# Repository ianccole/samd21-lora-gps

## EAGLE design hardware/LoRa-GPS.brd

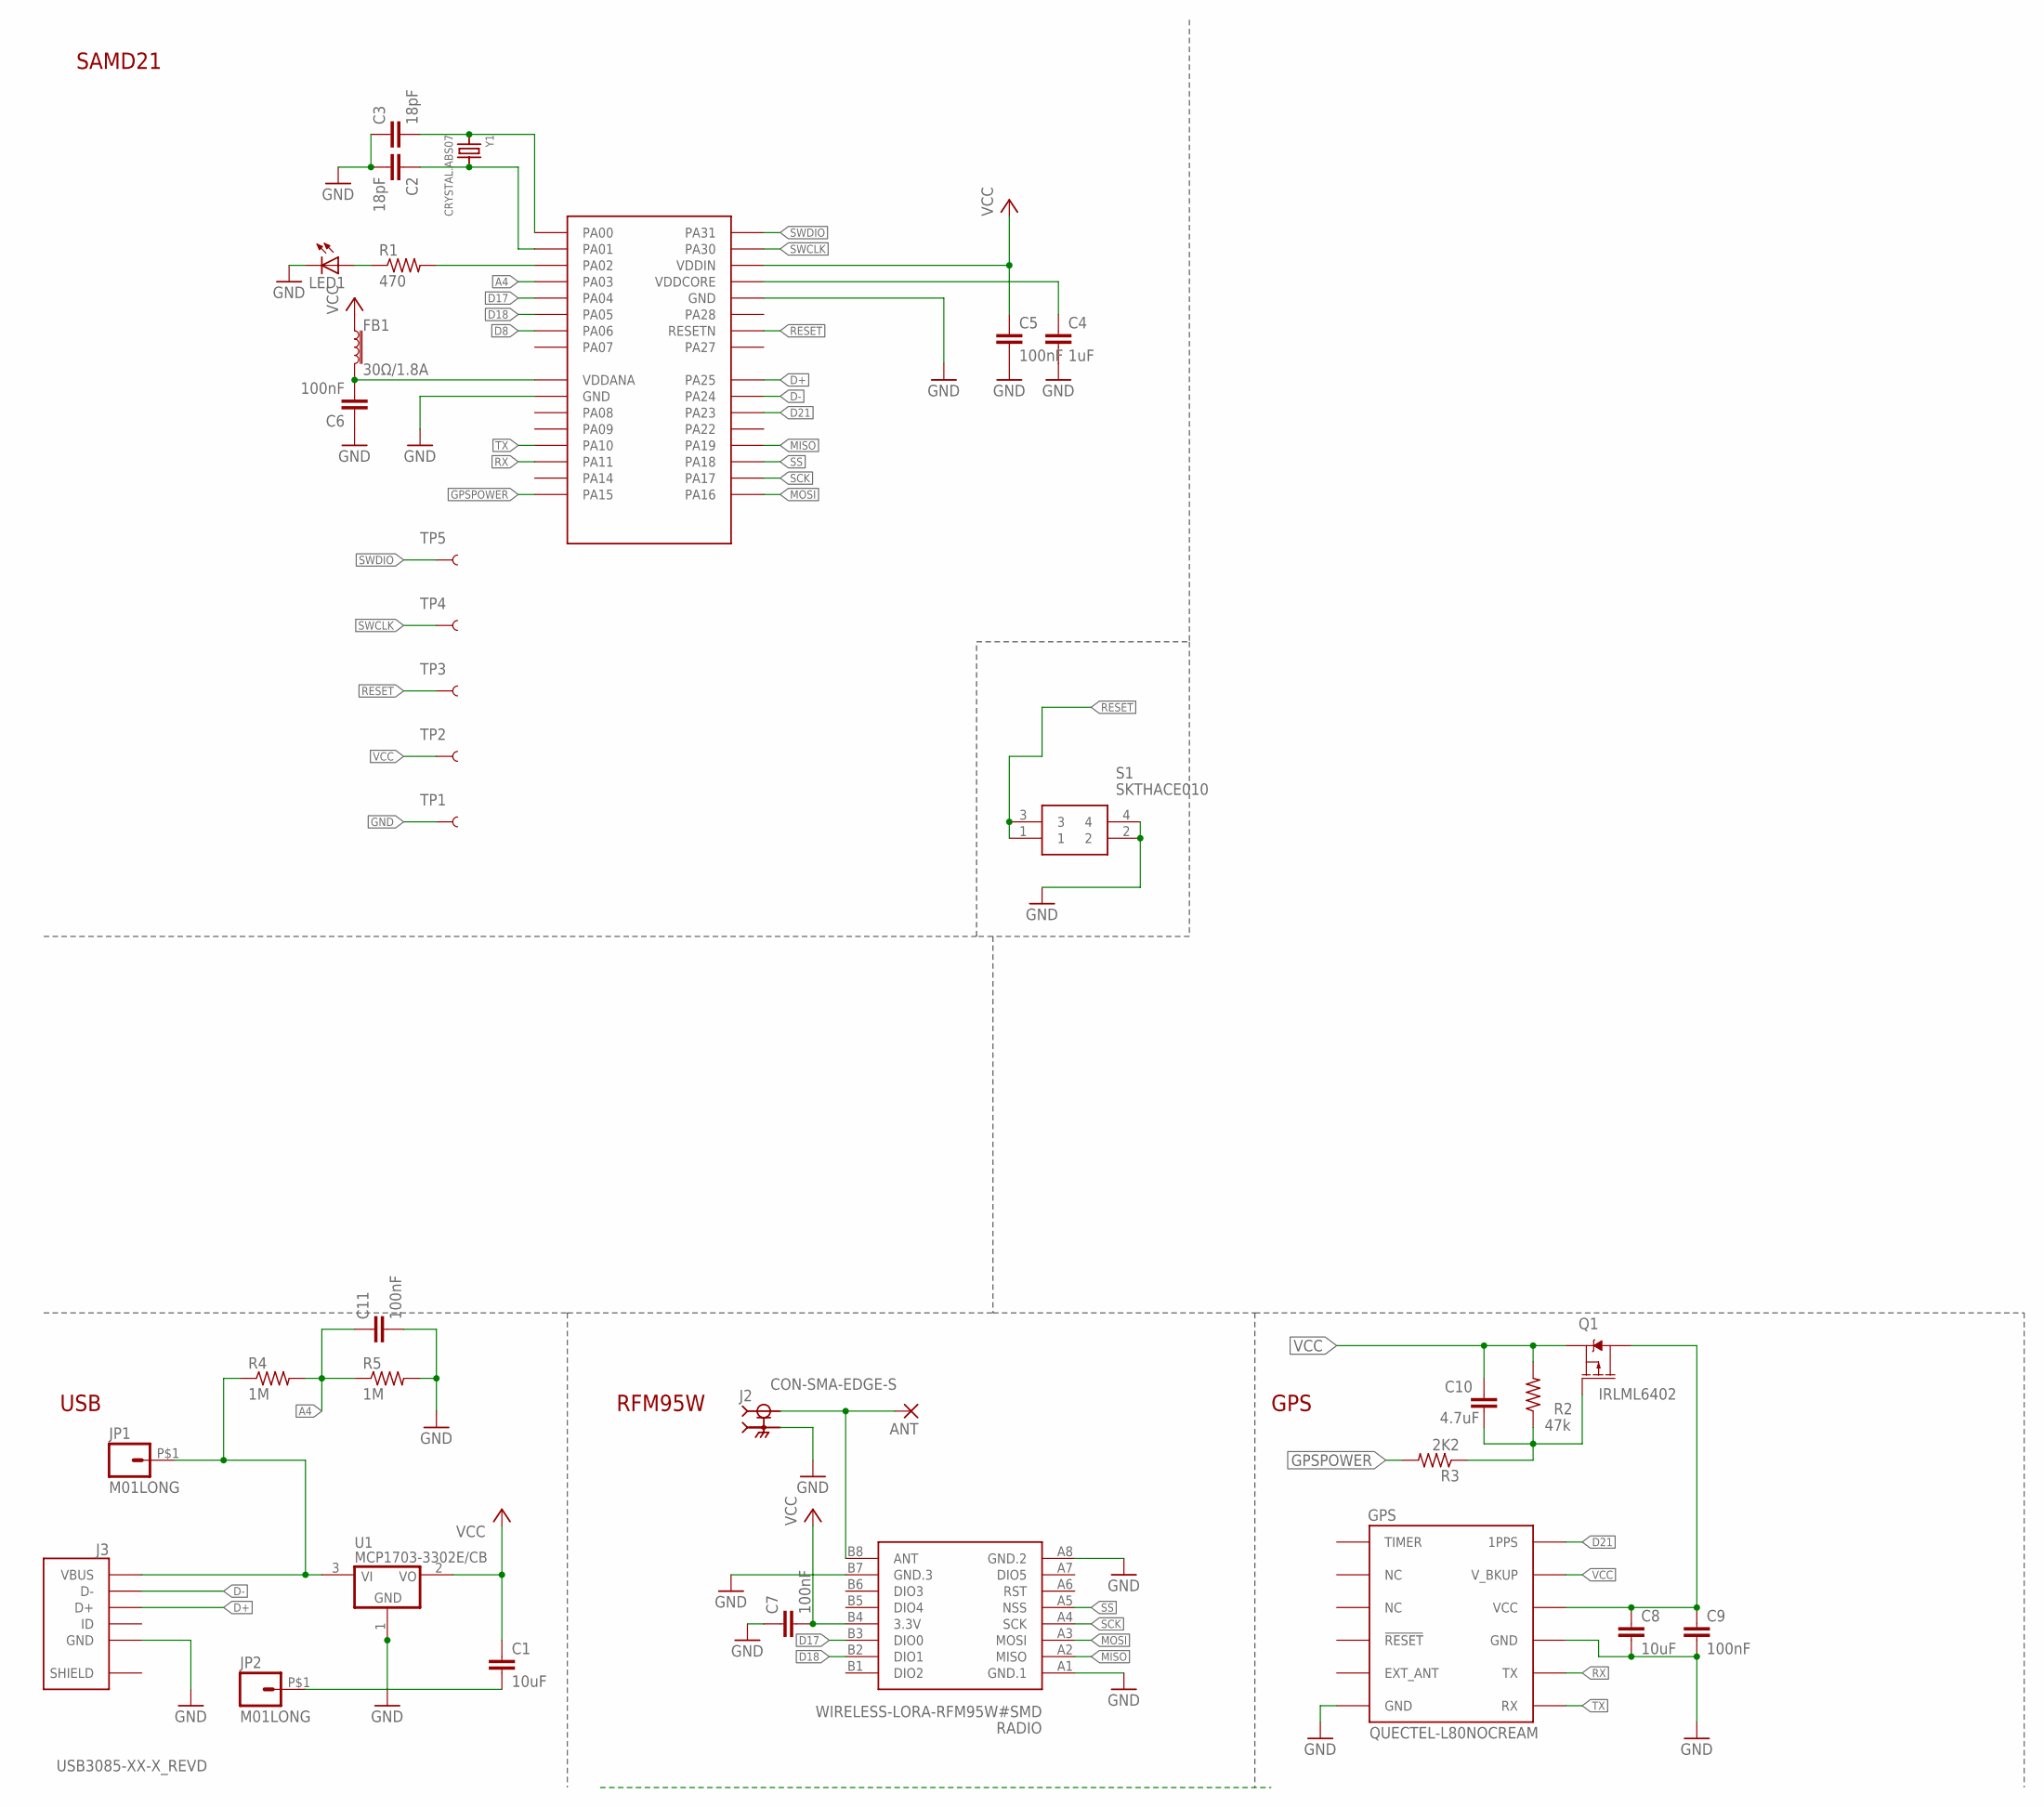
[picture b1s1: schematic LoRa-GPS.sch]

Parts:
ANT: 1,6/0,8
C1, C8: 10uF; C0603-THINCREAM
C2, C3: 18pF; C0603-THINCREAM
C4: 1uF; C0603-THINCREAM
C5, C6, C7, C9, C11: 100nF; C0603-THINCREAM; MPN 02016D104KAT2A
C10: 4.7uF; C0603-THINCREAM
FB1: 30Ω/1.8A; 0603
GPS: QUECTEL-L80NOCREAM; QUECTEL-L80-NOCREAM
J2: CON-SMA-EDGE-S; RFSOLUTIONS_CON-SMA-EDGE-S
J3: USB3085-XX-X_REVD; GCT_USB3085-XX-X_REVD
JP1, JP2: M01LONG; 1X01_LONG
LED1: LEDCHIPLED_0805_THINCREAM; CHIPLED_0805-THINCREAM
Q1: IRLML6402; SOT23-3
R1: 470; R0603-THINCREAM
R2: 47k; R0603-THINCREAM
R3: 2K2; R0603-THINCREAM
R4, R5: 1M; R0603
RADIO: WIRELESS-LORA-RFM95W#SMD
S1: SKTHACE010
SAMD21: ATSAMD21E18A-AU; 32-TQFP
TP1: GND; PAD.03X.05
TP2: VCC; PAD.03X.05
TP3, TP4, TP5: TEST-POINT3X5; PAD.03X.05
U1: MCP1703-3302E/CB; SOT23A_MICROCHIP_CB
Y1: CRYSTAL.ABS07; ABS07

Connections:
A4: C11.1, R4.2, R5.1, SAMD21.4 (PA03)
ANT: ANT.1, J2.1, RADIO.B8 (ANT)
D8: SAMD21.7 (PA06)
D17: RADIO.B3 (DIO0), SAMD21.5 (PA04)
D18: RADIO.B2 (DIO1), SAMD21.6 (PA05)
D21: GPS.6 (1PPS), SAMD21.22 (PA23)
D+: J3.3 (D+), SAMD21.24 (PA25)
D-: J3.2 (D-), SAMD21.23 (PA24)
GND: C1.2, C2.2, C3.1, C4.2, C5.2, C6.1, C7.1, C8.2, C9.2, C11.2, GPS.3 (GND), GPS.12 (GND), J2.G1 (2), J2.G2 (2), J2.G3 (2), J2.G4 (2), J3.5 (GND), JP2.P$1, LED1.C, R5.2, RADIO.A1 (GND.1), RADIO.A8 (GND.2), RADIO.B7 (GND.3), S1.2, S1.4, SAMD21.10 (GND), SAMD21.28 (GND), TP1.P$1, U1.1 (GND)
GPSPOWER: R3.2, SAMD21.16 (PA15)
MISO: RADIO.A2 (MISO), SAMD21.20 (PA19)
MOSI: RADIO.A3 (MOSI), SAMD21.17 (PA16)
unnamed: C6.2, FB1.2, SAMD21.9 (VDDANA)
unnamed: C2.1, SAMD21.2 (PA01), Y1.2
unnamed: C3.2, SAMD21.1 (PA00), Y1.1
unnamed: LED1.A, R1.1
unnamed: C4.1, SAMD21.29 (VDDCORE)
unnamed: R1.2, SAMD21.3 (PA02)
unnamed: C8.1, C9.1, GPS.4 (VCC), Q1.3 (D)
unnamed: C10.2, Q1.1 (G), R2.1, R3.1
RESET: S1.1, S1.3, SAMD21.26 (RESETN), TP3.P$1
RX: GPS.2 (TX), SAMD21.14 (PA11)
SCK: RADIO.A4 (SCK), SAMD21.18 (PA17)
SHIELD: J3.6 (SHIELD), J3.7 (SHIELD), J3.8 (SHIELD), J3.9 (SHIELD)
SS: RADIO.A5 (NSS), SAMD21.19 (PA18)
SWCLK: SAMD21.31 (PA30), TP4.P$1
SWDIO: SAMD21.32 (PA31), TP5.P$1
TX: GPS.1 (RX), SAMD21.13 (PA10)
VCC: C1.1, C5.1, C7.2, C10.1, FB1.1, GPS.5 (V_BKUP), Q1.2 (S), R2.2, RADIO.B4 (3.3V), SAMD21.30 (VDDIN), TP2.P$1, U1.2 (VO)
VIN: J3.1 (VBUS), JP1.P$1, R4.1, U1.3 (VI)

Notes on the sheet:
SAMD21
USB
RFM95W
GPS

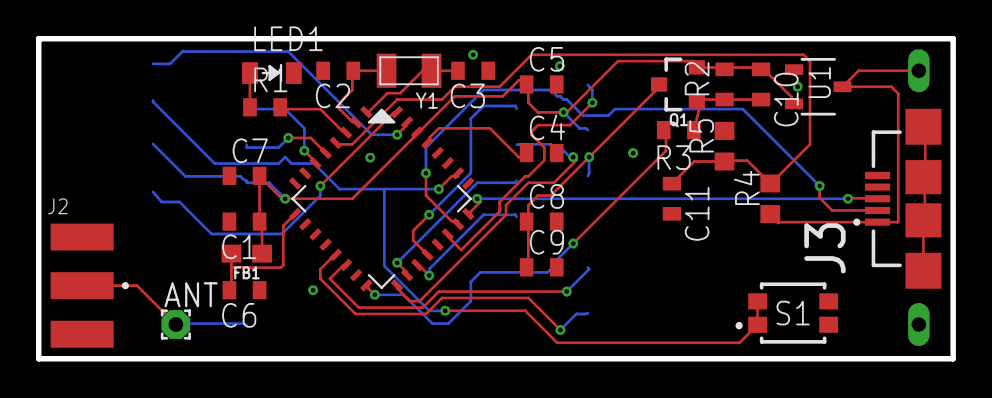
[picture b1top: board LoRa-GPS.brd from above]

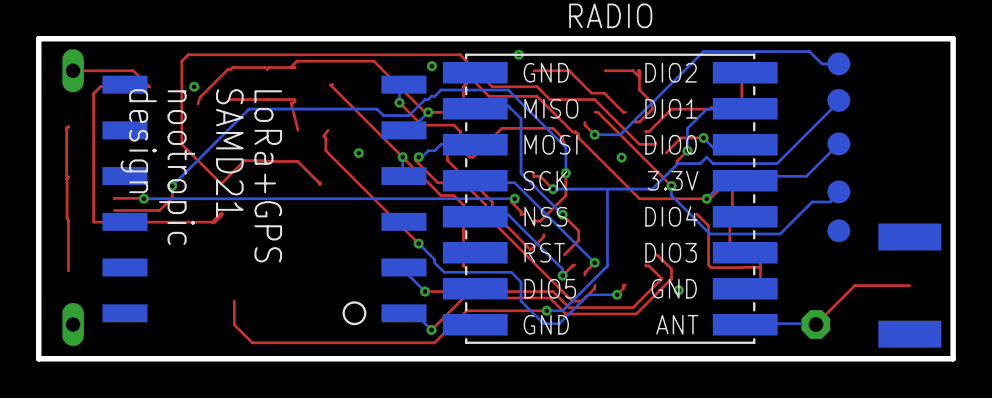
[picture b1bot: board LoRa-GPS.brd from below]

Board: 2 copper layers, 50.8 x 17.8 mm, 35 parts (7 on the bottom side), 29 nets.

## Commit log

2020-07-07 lipo
2020-07-07 add lines
2020-07-07 tidy
2020-07-14 remove DRC warnings
2020-07-26 remove switch move TP's
2020-07-27 tinker
2020-08-10 add gps power switch
2020-08-10 add and route gps vcc switch
2020-08-10 move GPS caps to bottom layer
2020-08-13 equal size label
2020-08-13 RF and GPS underside
2020-08-13 tidy GPS caps routing
2020-08-13 all vias 0.01
2020-08-14 add GPS VCC switch - check CPU pin is ok?
2020-08-17 amph usb conn
2020-08-17 add bom
2020-08-18 DRC correct. CAM output
2021-04-18 470 to 47k
2021-04-19 ripup
2021-04-19 Revert "ripup"
    This reverts commit 834d71edbbdf070d64fbb4b16cb78b1eed2d9a3e.
2021-04-19 move usb and psu to other side
2021-04-19 auto route
2021-04-19 manual route
2021-04-19 DRC pass
2021-04-20 bat mon. DRC keepout issue
2021-04-20 bat mon. DRC OK
2021-04-20 add FB for VDDANA
2021-04-21 bat mon. more pour. gerber gen

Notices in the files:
parts and their libraries:
diy-modules: Released under the Creative Commons Attribution 4.0 International License: http://creativecommons.org/licenses/by/4.0
SparkFun-Passives: Licensing: Creative Commons ShareAlike 4.0 International - https://creativecommons.org/licenses/by-sa/4.0
